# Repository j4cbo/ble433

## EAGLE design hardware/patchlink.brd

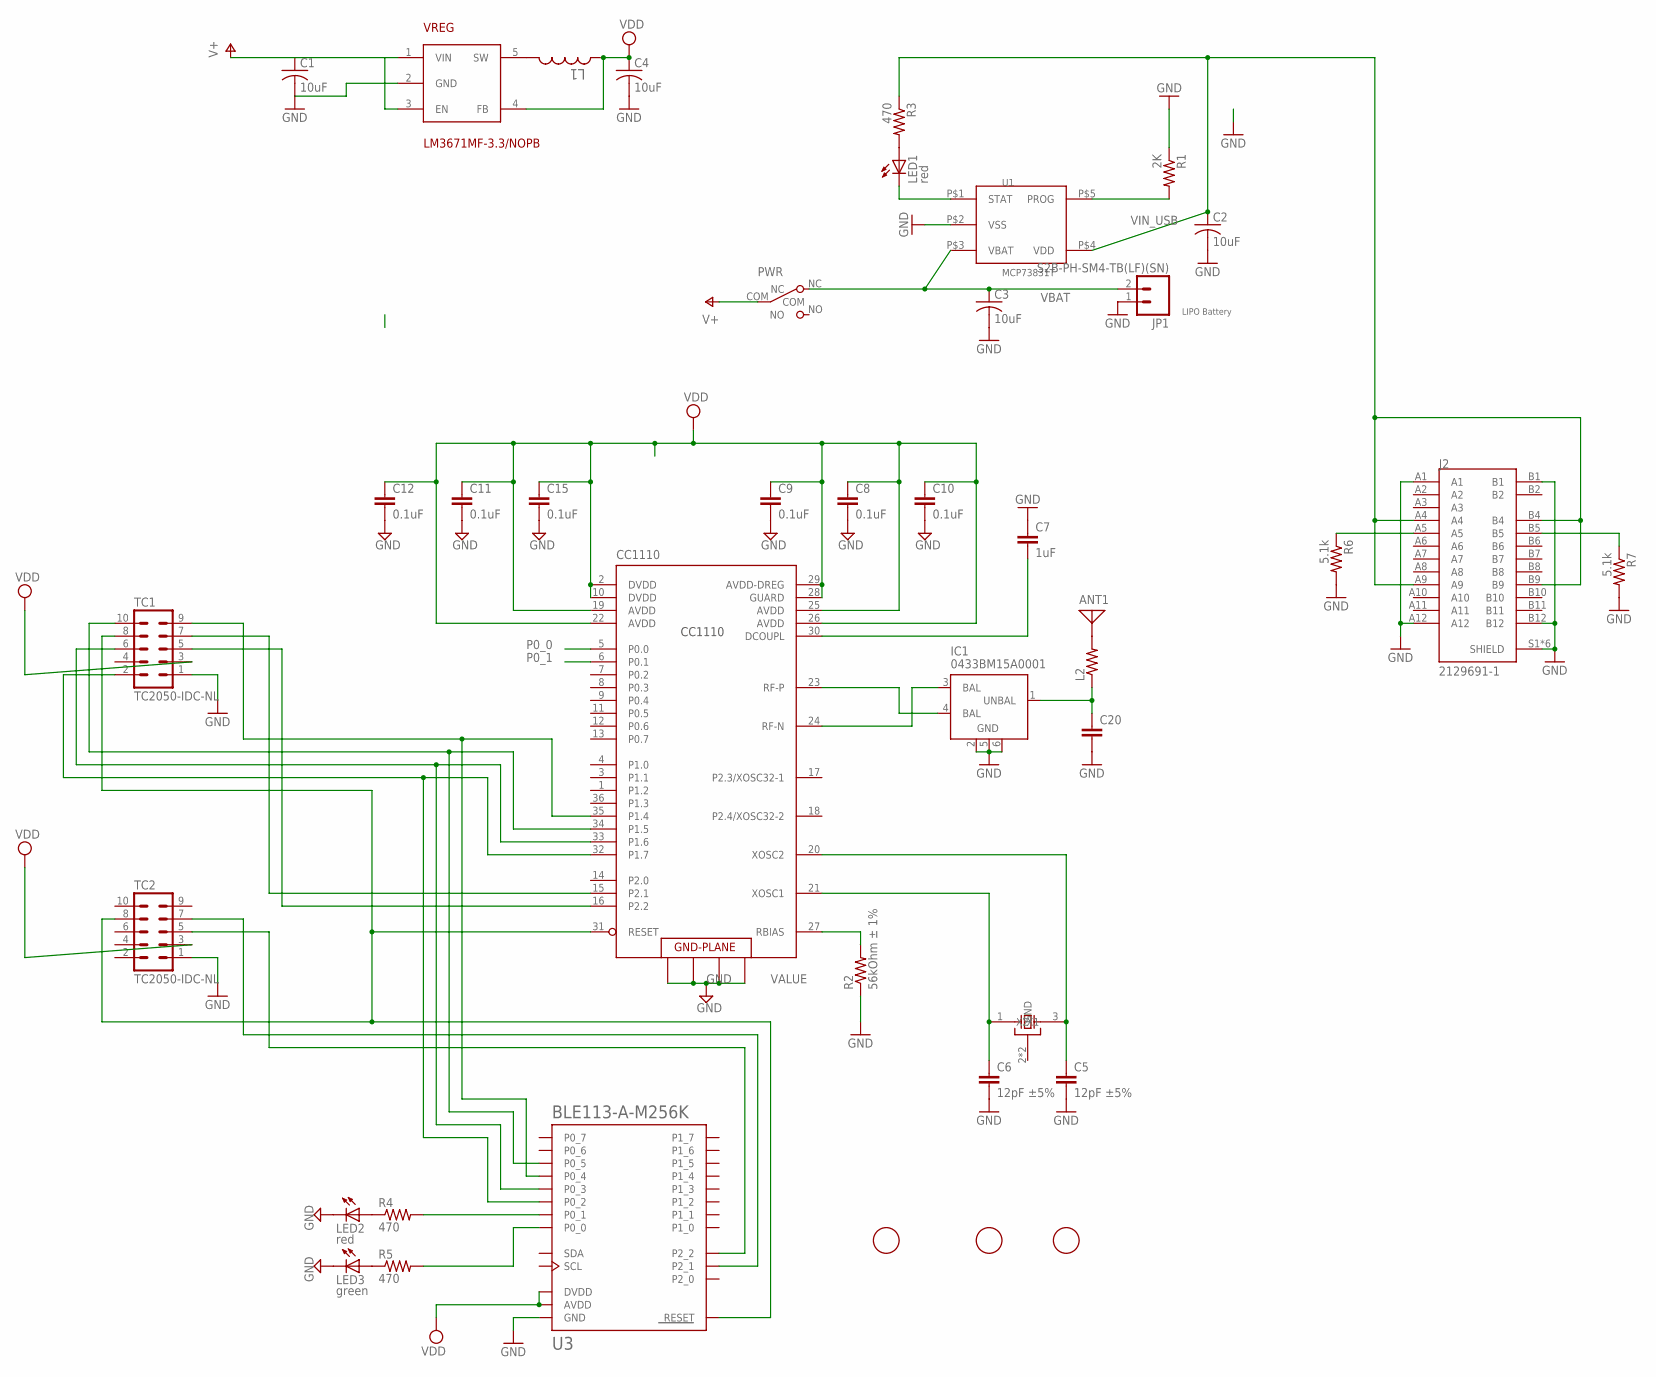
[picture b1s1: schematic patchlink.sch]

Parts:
ANT1: ANTENNASMT; 0433AT62A0020
C1, C2, C3, C4: 10uF; C1206
C5, C6: 12pF ±5%; C0402K
C7: 1uF; C0402
C8, C9, C10, C11, C12, C15: 0.1uF; C0402
C20: C-EUC0402; C0402
CC1110: CC1110F32RHHR; QLP-36_UPDATE
FID1, FID2, FID3: FIDUCIAL; FIDUCIAL_1MM
IC1: 0433BM15A0001; 0915BM15A0001
J2: 2129691-1; TE_2129691-1
JP1: S2B-PH-SM4-TB(LF)(SN); JST-2-SMD
L1: 2.2 uH; L2825P
L2: R-US_R0402; R0402
LED1, LED2: red; SML0603
LED3: green; SML0603
PWR: SW_SLIDE; SLIDE_SWITCH_SMD
R1: 2K; R0402
R2: 56kOhm ± 1%; R0402
R3, R4, R5: 470; R0402
R6, R7: 5.1k; R0402
TC1, TC2: TC2050-IDC-NL
U1: MCP73831T; 5PIN_SOT23
U3: BLE113-A-M256K; BLE113-A
VREG: LM3671MF-3.3/NOPB; SOT23-5
X1: 24MHz 8pF 10ppm -20C +70C; CTS_32X25

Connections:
DC: CC1110.16 (P2.2), TC1.5
DC_BLE: TC2.5, U3.P2_2
DD: CC1110.15 (P2.1), TC1.7
DD_BLE: TC2.7, U3.P2_1
GND: C1.2, C2.2, C3.2, C4.2, C5.2, C6.2, C7.1, C8.2, C9.2, C10.2, C11.2, C12.2, C15.2, C20.2, CC1110.37 (GND), CC1110.38 (GND), CC1110.39 (GND), CC1110.40 (GND), IC1.2 (GND), IC1.5 (GND), IC1.6 (GND), J2.A1, J2.A12, J2.B1, J2.B12, J2.S1 (SHIELD), J2.S2 (SHIELD), J2.S3 (SHIELD), J2.S4 (SHIELD), J2.S5 (SHIELD), J2.S6 (SHIELD), JP1.1 (2), LED2.C, LED3.C, R1.1, R2.1, R6.2, R7.2, TC1.1, TC2.1, U1.P$2 (VSS), U3.GND, U3.GND@2 (GND), U3.GND@3 (GND), U3.GND@4 (GND), U3.GND@5 (GND), U3.GND@6 (GND), U3.GND@7 (GND), U3.GND@8 (GND), U3.GND@9 (GND), U3.GND@10 (GND), VREG.2 (GND), X1.2 (GND), X1.4 (GND)
MISO: CC1110.32 (P1.7), TC1.2, U3.P0_2
MOSI: CC1110.33 (P1.6), TC1.6, U3.P0_3
unnamed: ANT1.P$1, L2.2
unnamed: LED1.C, U1.P$1 (STAT)
unnamed: R1.2, U1.P$5 (PROG)
unnamed: LED1.A, R3.2
unnamed: CC1110.24 (RF-N), IC1.3 (BAL)
unnamed: CC1110.23 (RF-P), IC1.4 (BAL)
unnamed: C20.1, IC1.1 (UNBAL), L2.1
unnamed: J2.A5, R6.1
unnamed: J2.B5, R7.1
unnamed: CC1110.27 (RBIAS), R2.2
unnamed: L1.2, VREG.5 (SW)
unnamed: C7.2, CC1110.30 (DCOUPL)
unnamed: C6.1, CC1110.21 (XOSC1), X1.1 (X1)
unnamed: C5.1, CC1110.20 (XOSC2), X1.3 (X2)
unnamed: LED2.A, R4.1
unnamed: LED3.A, R5.1
unnamed: R4.2, U3.P0_1
unnamed: R5.2, U3.P0_0
P0_0: CC1110.5 (P0.0)
P0_1: CC1110.6 (P0.1)
RESET: CC1110.31 (RESET), TC1.8, TC2.8, U3.RESET
SCK: CC1110.34 (P1.5), TC1.10, U3.P0_5
SSN: CC1110.35 (P1.4), TC1.9, U3.P0_4
V+: C1.1, PWR.COM, VREG.1 (VIN), VREG.3 (EN)
VBAT: C3.1, JP1.2 (1), PWR.NC, U1.P$3 (VBAT)
VDD: C4.1, C8.1, C9.1, C10.1, C11.1, C12.1, C15.1, CC1110.2 (DVDD), CC1110.10 (DVDD), CC1110.19 (AVDD), CC1110.22 (AVDD), CC1110.25 (AVDD), CC1110.26 (AVDD), CC1110.28 (GUARD), CC1110.29 (AVDD-DREG), L1.1, TC1.3, TC2.3, U3.AVDD, U3.DVDD, VREG.4 (FB)
VIN_USB: C2.1, J2.A4, J2.A9, J2.B4, J2.B9, R3.1, U1.P$4 (VDD)

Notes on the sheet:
LIPO Battery
CC1110

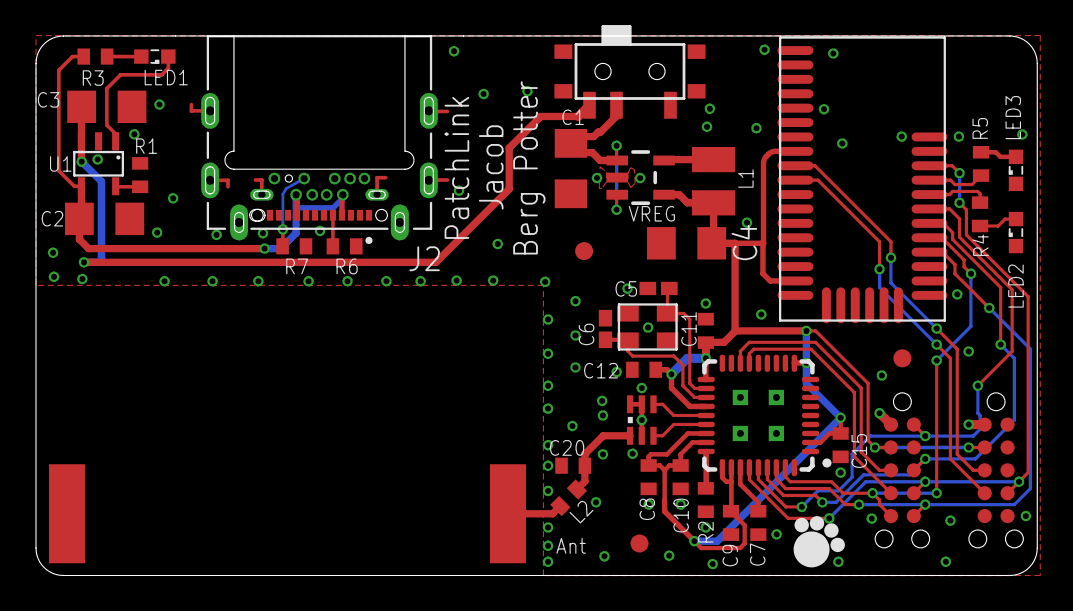
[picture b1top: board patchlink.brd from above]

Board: 2 copper layers, 55.6 x 30.0 mm, 41 parts (1 on the bottom side), 32 nets.

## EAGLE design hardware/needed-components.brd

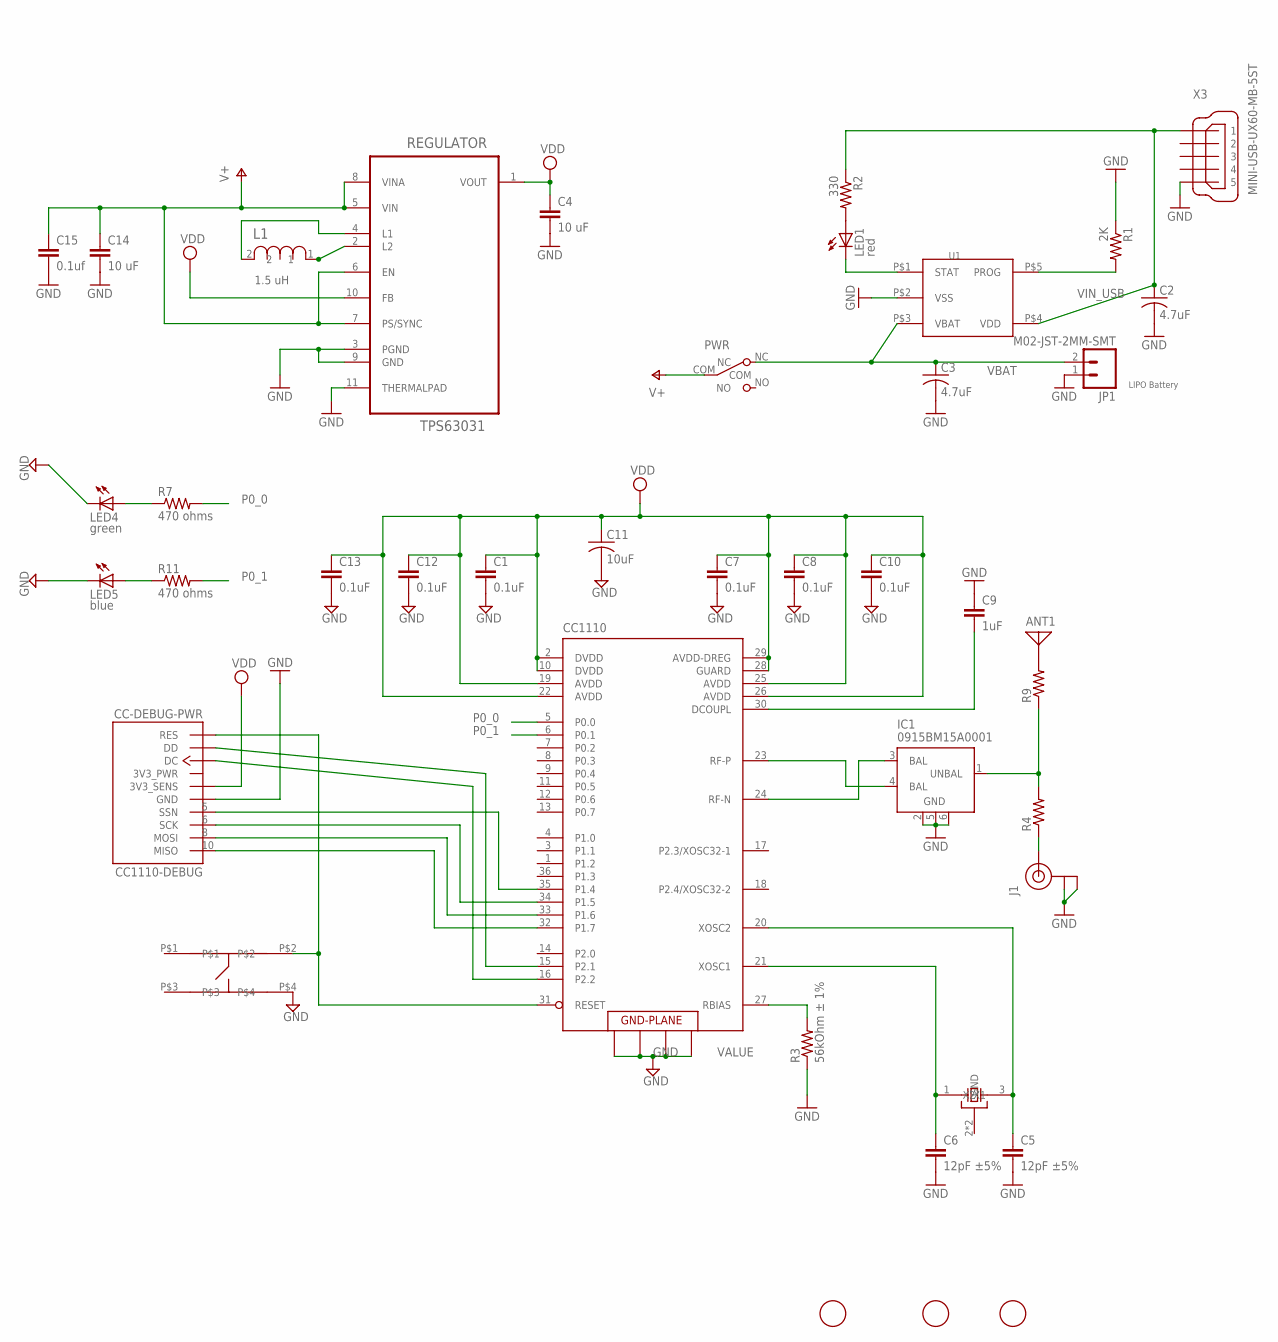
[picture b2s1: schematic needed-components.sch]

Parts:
ANT1: ANTENNA; PAD-01
C1, C7, C8, C10, C12, C13: 0.1uF; C0402
C2, C3: 4.7uF; C0603K
C4: 10 uF; C0805K
C5, C6: 12pF ±5%; C0402K
C9: 1uF; C0402K
C11: 10uF; C0805K
C14: 10 uF; C0603
C15: 0.1uf; C0402
CC1110: CC1110; QLP-36_UPDATE
CC1110-DEBUG: CC-DEBUG-PWR; CC-P05
FID1, FID2, FID3: FIDUCIAL; FIDUCIAL_1MM
IC1: 0915BM15A0001
J1: U.FL
JP1: M02-JST-2MM-SMT; JST-2-SMD
L1: 1.5 uH; INDC1610X12N; MPN MLF1608A1R5KTD25
LED1: red; SML0603
LED4: green; SML0603
LED5: blue; SML0603
PWR: SW_SLIDE; SLIDE_SWITCH_SMD
R1: 2K; R0402
R2: 330; R0402
R3: 56kOhm ± 1%; R0402
R4, R9: R-US_R0402; R0402
R7, R11: 470 ohms; R0402
REGULATOR: TPS63031; SON50P260X260X80-11N; MPN TPS63031
U1: MCP73831; 5PIN_SOT23
U$2: TACTILE_SWITCH; PTS540
X1: 24MHz 8pF 10ppm -20C +70C; CTS_32X25
X3: MINI-USB-UX60-MB-5ST; UX60-MB-5ST

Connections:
DC: CC1110.16 (P2.2), CC1110-DEBUG.3 (DC)
DD: CC1110.15 (P2.1), CC1110-DEBUG.4 (DD)
GND: C1.2, C2.2, C3.2, C4.2, C5.2, C6.2, C7.2, C8.2, C9.1, C10.2, C11.2, C12.2, C13.2, C14.2, C15.2, CC1110.37 (GND), CC1110.38 (GND), CC1110.39 (GND), CC1110.40 (GND), CC1110-DEBUG.1 (GND), IC1.2 (GND), IC1.5 (GND), IC1.6 (GND), J1.P$1 (GND), J1.P$2 (GND), JP1.1 (2), LED4.C, LED5.C, R1.1, R3.1, REGULATOR.3 (PGND), REGULATOR.9 (GND), REGULATOR.11 (THERMALPAD), U1.P$2 (VSS), U$2.P$4, X1.2 (GND), X1.4 (GND), X3.5
MISO: CC1110.32 (P1.7), CC1110-DEBUG.10 (MISO)
MOSI: CC1110.33 (P1.6), CC1110-DEBUG.8 (MOSI)
unnamed: L1.1, REGULATOR.2 (L2)
unnamed: LED1.C, U1.P$1 (STAT)
unnamed: R1.2, U1.P$5 (PROG)
unnamed: LED1.A, R2.2
unnamed: CC1110.24 (RF-N), IC1.3 (BAL)
unnamed: L1.2, REGULATOR.4 (L1)
unnamed: CC1110.23 (RF-P), IC1.4 (BAL)
unnamed: J1.P$3 (SIGNAL), R4.1
unnamed: IC1.1 (UNBAL), R4.2, R9.1
unnamed: ANT1.1, R9.2
unnamed: CC1110.27 (RBIAS), R3.2
unnamed: C9.2, CC1110.30 (DCOUPL)
unnamed: C6.1, CC1110.21 (XOSC1), X1.1 (X1)
unnamed: C5.1, CC1110.20 (XOSC2), X1.3 (X2)
unnamed: LED4.A, R7.1
unnamed: LED5.A, R11.1
P0_0: CC1110.5 (P0.0), R7.2
P0_1: CC1110.6 (P0.1), R11.2
RESET: CC1110.31 (RESET), CC1110-DEBUG.7 (RES), U$2.P$2
SCK: CC1110.34 (P1.5), CC1110-DEBUG.6 (SCK)
SSN: CC1110.35 (P1.4), CC1110-DEBUG.5 (SSN)
V+: C14.1, C15.1, PWR.COM, REGULATOR.5 (VIN), REGULATOR.6 (EN), REGULATOR.7 (PS/SYNC), REGULATOR.8 (VINA)
VBAT: C3.1, JP1.2 (1), PWR.NC, U1.P$3 (VBAT)
VDD: C1.1, C4.1, C7.1, C8.1, C10.1, C11.1, C12.1, C13.1, CC1110.2 (DVDD), CC1110.10 (DVDD), CC1110.19 (AVDD), CC1110.22 (AVDD), CC1110.25 (AVDD), CC1110.26 (AVDD), CC1110.28 (GUARD), CC1110.29 (AVDD-DREG), CC1110-DEBUG.2 (3V3_SENS), REGULATOR.1 (VOUT), REGULATOR.10 (FB)
VIN_USB: C2.1, R2.1, U1.P$4 (VDD), X3.1

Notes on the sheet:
LIPO Battery

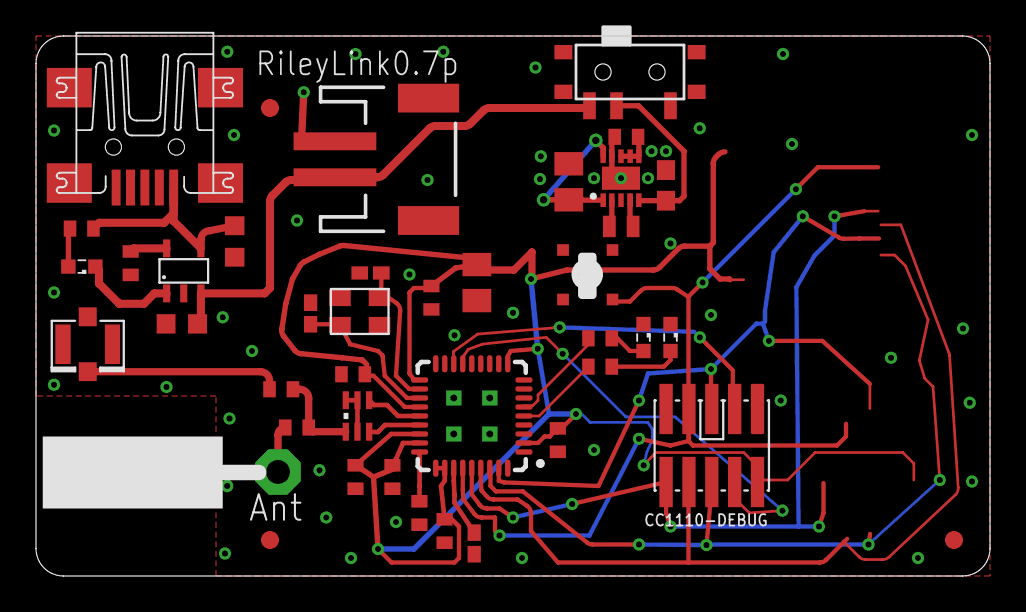
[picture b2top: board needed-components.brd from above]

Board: 2 copper layers, 53.0 x 30.0 mm, 41 parts (0 on the bottom side), 30 nets.

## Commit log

2019-04-27 JDBP changes: BOM adjustments, microUSB
2019-04-27 More trace and part packing; DRC approvals
2019-05-24 More changes
2019-05-24 PatchLink
2019-05-29 Increase radius of cutter
2019-05-29 Remove unused layers. Approve remaining DRC plated slot issues.

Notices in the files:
parts and their libraries:
parts: Package design from "pretty-eagle-libs" at https://github.com/esden/pretty-eagle-libs/blob/master/pel_misc.lbr by @esden at Github. (CC-BY-SA-3.0)
SparkFun-Connectors: Licensing: Creative Commons ShareAlike 4.0 International - https://creativecommons.org/licenses/by-sa/4.0
